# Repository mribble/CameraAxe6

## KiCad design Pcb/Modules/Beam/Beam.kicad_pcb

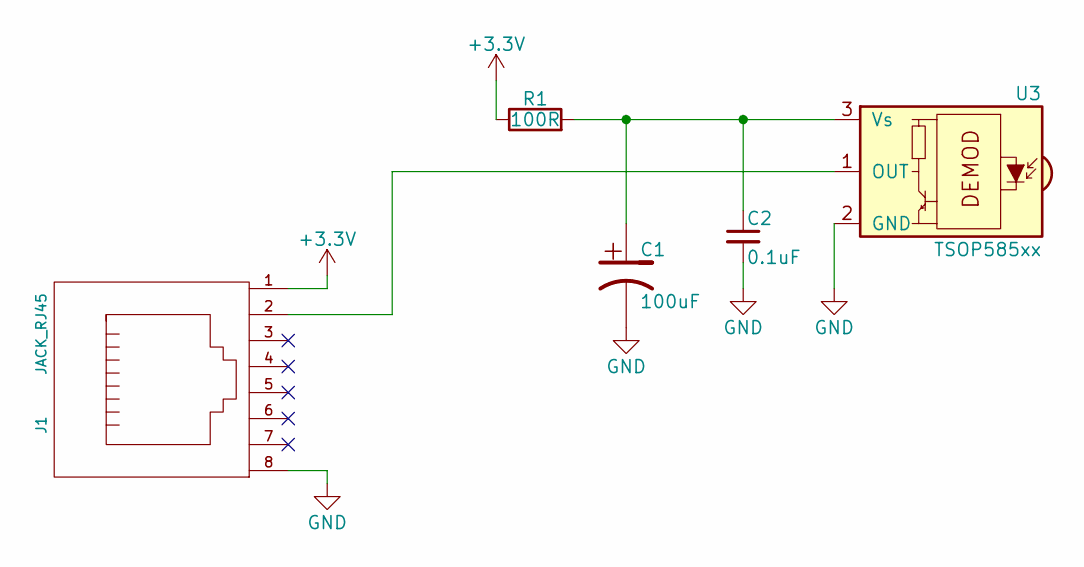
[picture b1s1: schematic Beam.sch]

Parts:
C1: 100uF; c_elec_6.3x5.7
C2: 0.1uF; R_0603
J1: JACK_RJ45; RJ45_pcbwing
R1: 100R; R_0603
U3: TSOP585xx; IRReceiver_Vishay_MINICAST-3pin

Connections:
+3V3: J1.1, R1.1
GND: C1.2, C2.2, J1.8, U3.2 (GND)
unnamed: C1.1, C2.1, R1.2, U3.3 (Vs)
unnamed: J1.2, U3.1 (OUT)

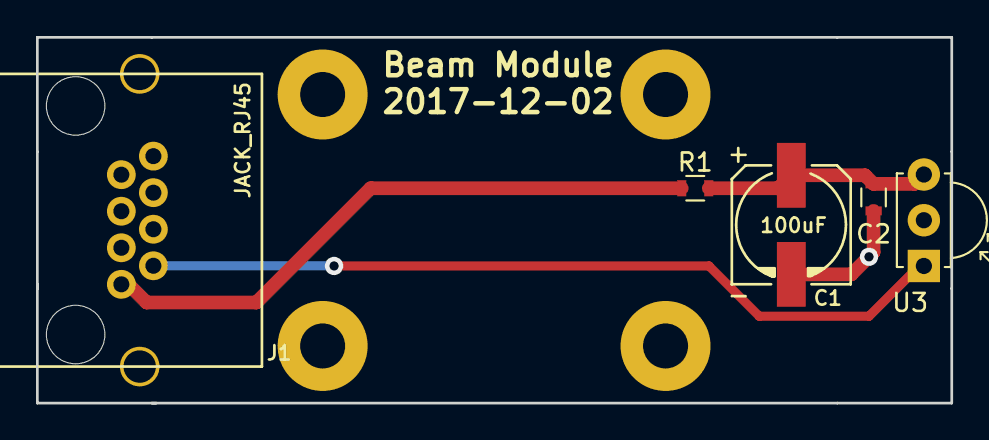
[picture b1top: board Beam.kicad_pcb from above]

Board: 2 copper layers, 50.8 x 20.3 mm, 9 parts (0 on the bottom side), 4 nets.

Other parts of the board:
X1, X2, X3, X4: HOLE; MountingHole_2.5mm_Pad

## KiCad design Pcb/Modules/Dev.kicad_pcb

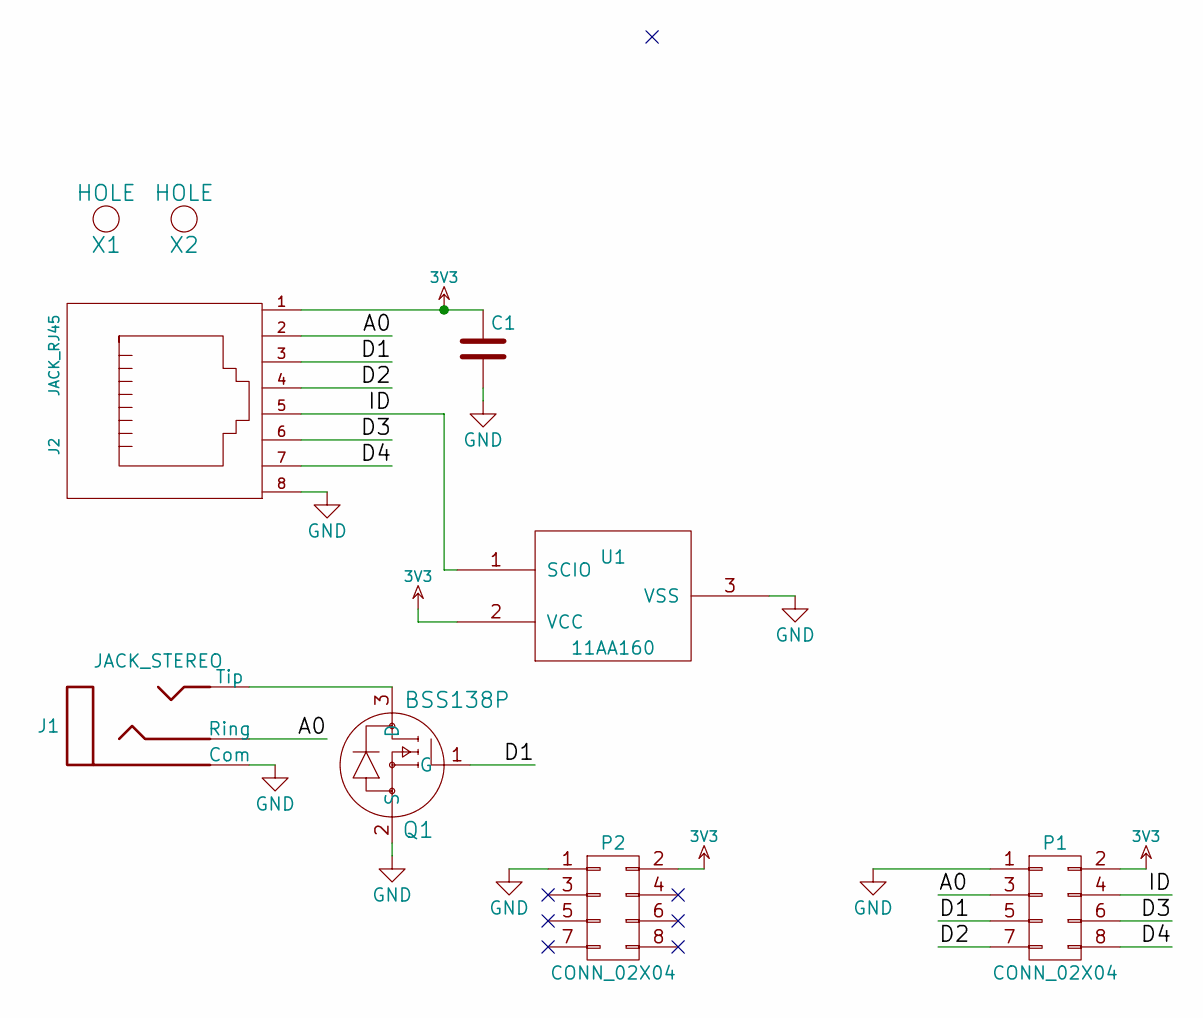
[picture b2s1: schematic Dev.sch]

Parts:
C1: C; c_1206
J1: JACK_STEREO; 161-3334-E_Big_Pad
J2: JACK_RJ45; RJ45_RJHSE-5080
P1, P2: CONN_02X04; Socket_Strip_Straight_2x04_Pitch2.54mm
Q1: BSS138P; SOT23
U1: 11AA160; SOT-23_11AA160
X1, X2: HOLE; HOLE_3.0mm

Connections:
3V3: C1.1, J2.1, P1.2, P2.2, U1.2 (VCC)
/A0: J1.1 (Ring), J2.2, P1.3
/D1: J2.3, P1.5, Q1.1 (G)
/D2: J2.4, P1.7
/D3: J2.6, P1.6
/D4: J2.7, P1.8
/ID: J2.5, P1.4, U1.1 (SCIO)
GND: C1.2, J1.3 (Com), J2.8, P1.1, P2.1, Q1.2 (S), U1.3 (VSS)
unnamed: J1.2 (Tip), Q1.3 (D)

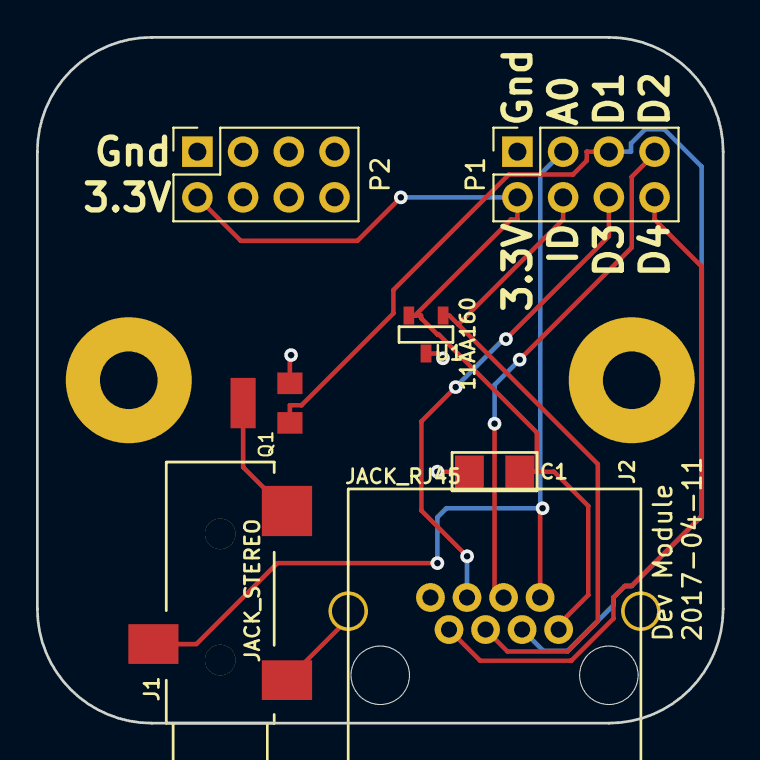
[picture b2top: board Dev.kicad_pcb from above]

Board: 2 copper layers, 38.1 x 38.1 mm, 9 parts (0 on the bottom side), 9 nets.

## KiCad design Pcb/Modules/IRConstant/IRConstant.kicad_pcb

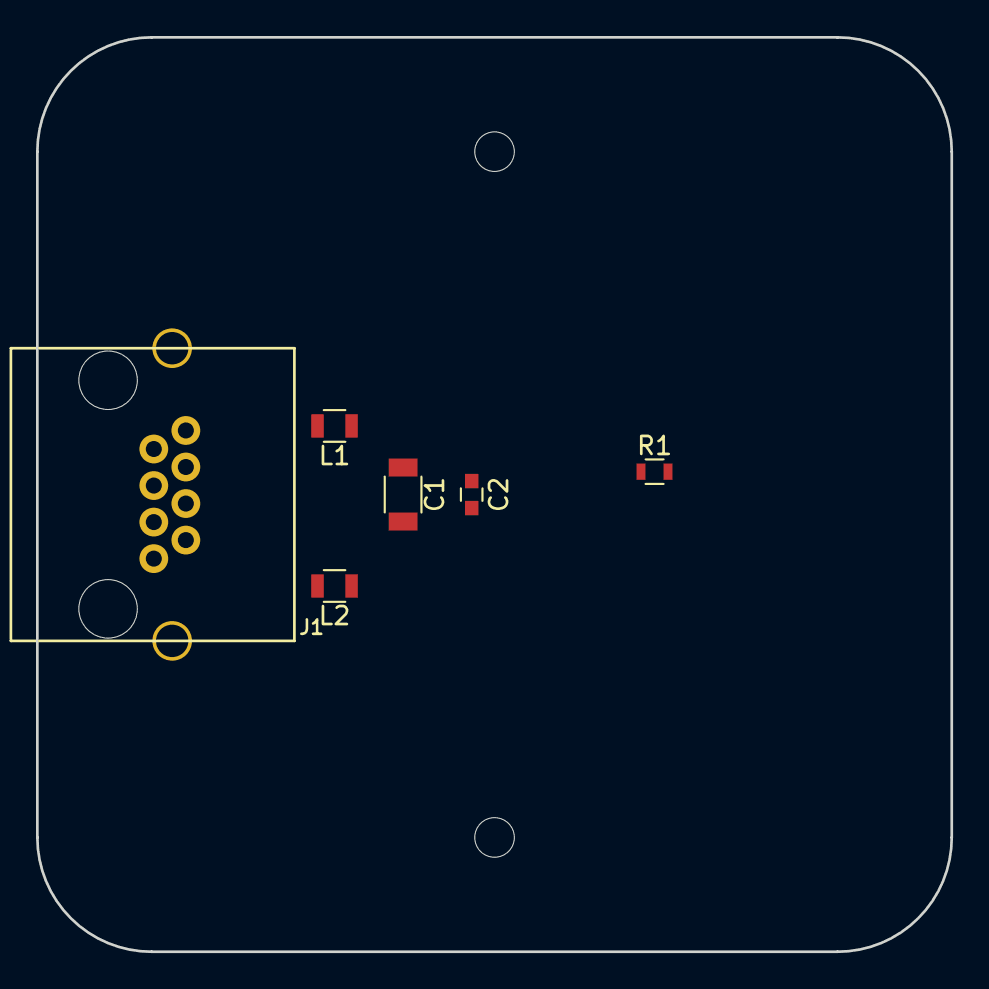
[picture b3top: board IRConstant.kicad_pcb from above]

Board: 2 copper layers, 50.8 x 50.8 mm, 6 parts (0 on the bottom side), 4 nets, no tracks yet.

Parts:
C1: 10uF; C_1206
C2: 0.1uF; C_0603
J1: JACK_RJ45; RJ45_pcbwing
L1, L2: Ferrite_Bead; R_0805
R1: R; R_0603

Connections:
+3V3: C1.1, C2.1, L1.1
GND: C1.2, C2.2, L2.1
unnamed: J1.1, L2.2
unnamed: J1.8, L1.2

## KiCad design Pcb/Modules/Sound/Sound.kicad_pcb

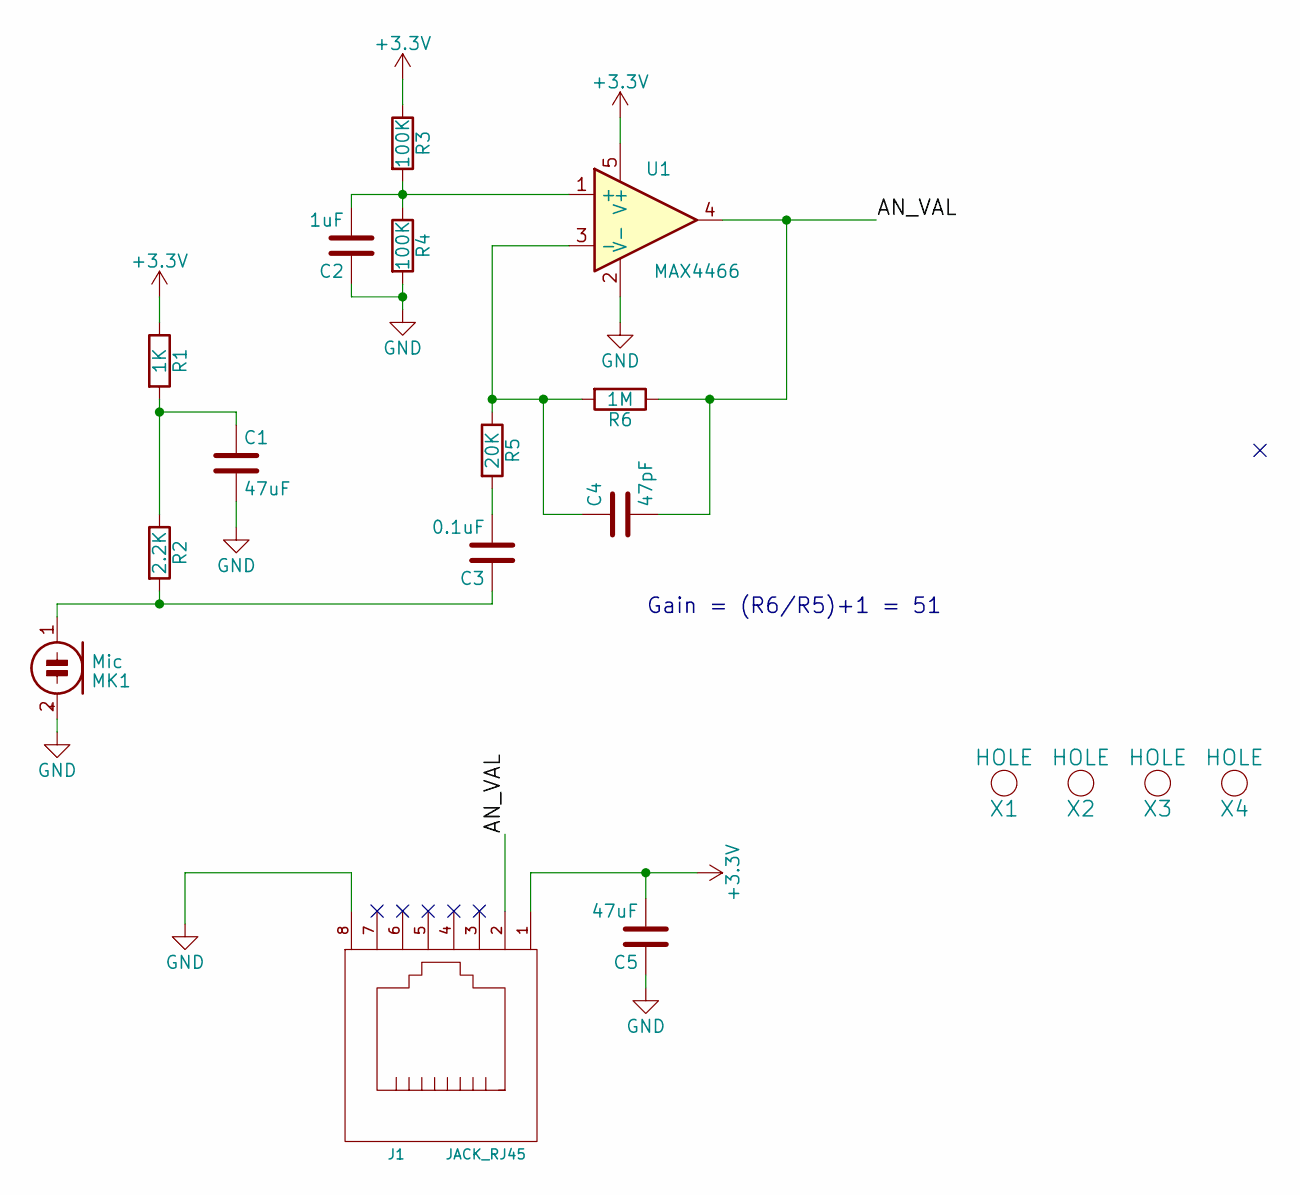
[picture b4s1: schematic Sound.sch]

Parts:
C1, C5: 47uF; C_1206
C2: 1uF; C_0603
C3: 0.1uF; C_0603
C4: 47pF; C_0603
J1: JACK_RJ45; RJ45_pcbwing
MK1: Mic; MIC_CMA-4544PF
R1: 1K; R_0603
R2: 2.2K; R_0603
R3, R4: 100K; R_0603
R5: 20K; R_0603
R6: 1M; R_0603
U1: MAX4466; SOT-353_SC-70-5
X1, X2, X3, X4: HOLE; MountingHole_2.5mm_Pad

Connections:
+3V3: C5.2, J1.1, R1.1, R3.1, U1.5 (V+)
/AN_VAL: C4.2, J1.2, R6.1, U1.4
GND: C1.2, C2.1, C5.1, J1.8, MK1.2 (+), R4.2, U1.2 (V-)
unnamed: C1.1, R1.2, R2.1
unnamed: C2.2, R3.2, R4.1, U1.1 (+)
unnamed: C3.1, MK1.1 (-), R2.2
unnamed: C3.2, R5.2
unnamed: C4.1, R5.1, R6.2, U1.3 (-)

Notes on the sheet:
Gain = (R6/R5)+1 = 51

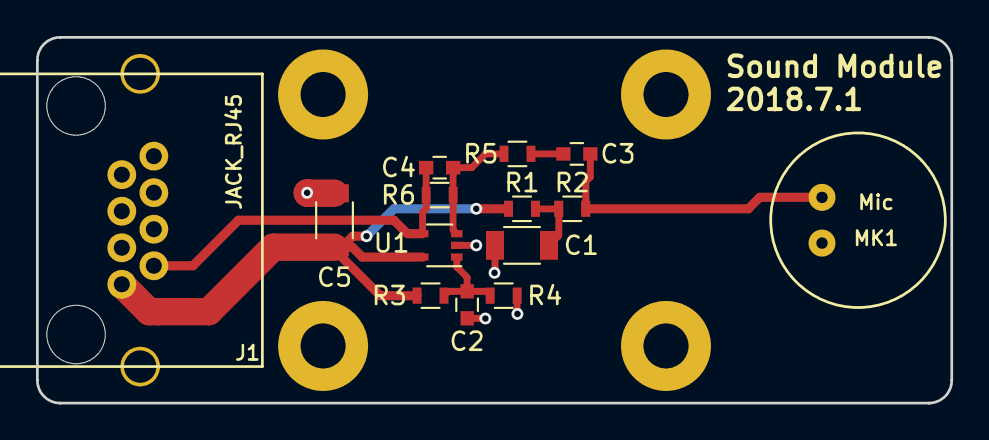
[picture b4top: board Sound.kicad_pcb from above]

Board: 2 copper layers, 50.8 x 20.3 mm, 18 parts (0 on the bottom side), 8 nets.

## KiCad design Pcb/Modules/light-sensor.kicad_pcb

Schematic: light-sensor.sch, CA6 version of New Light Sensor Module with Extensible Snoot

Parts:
C1: 10uF; c_1206
J1: JACK_RJ45; RJ45_pcbwing
J2: JACK_STEREO; 161-3334-E_Big_Pad
Q1: TEPT4400; PhotoTrans_Conn_Pads_1x02_Pitch2.54mm
Q2: MMBT2907ALT1G; SOT-23
R1, R3: 1K; SM0603_Resistor
R2: 174 1%; SM0805_Resistor
RV1: 20K; Potentiometer_Alps_RK09L_Single_Vertical
X1, X2, X3, X4: HOLE; MountingHole_2.2mm_M2

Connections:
3V3: C1.1, J1.1, Q1.3, Q2.2
/AN1: J1.2, R1.1
/D1: J1.3, R3.1
/D2: J1.4
/D3: J1.6
/D4: J1.7
/ID: J1.5
GND: C1.2, J1.8, J2.3 (Com), R2.2
unnamed: J2.2 (Tip), Q2.3
unnamed: Q1.1, R1.2, RV1.1
unnamed: Q2.1, R3.2
unnamed: R2.1, RV1.2, RV1.3

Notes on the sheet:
3.5mm Jack for Laser Power
Sensitivity Adj.
CA6 version of New Light Sensor Module with Extensible Snoot
just wire pads on board photo trans. connected via wires
Choose R2 for MAX current of 20mA 180 = 18.3 mA 174 = 18.9 mA 169 = 19.5 mA

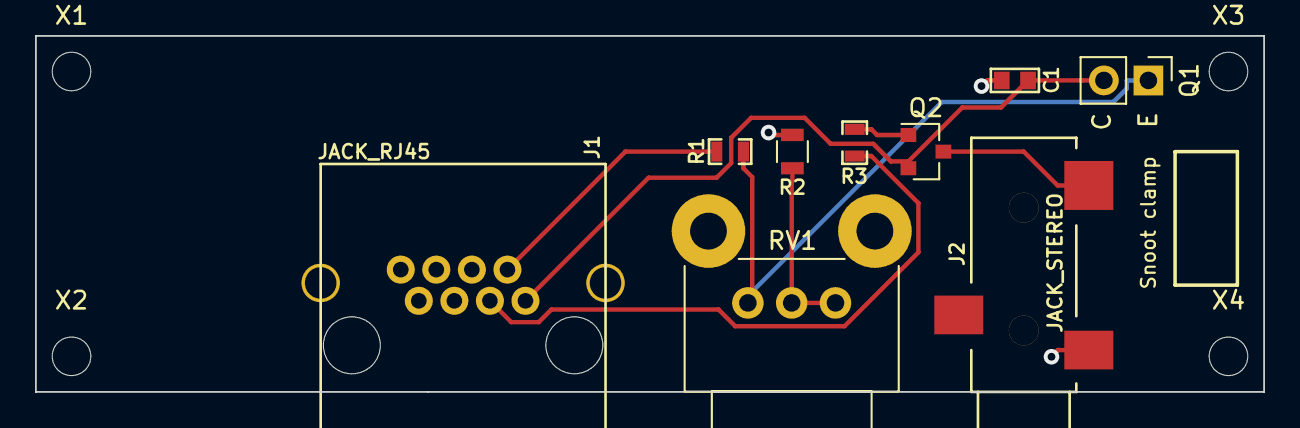
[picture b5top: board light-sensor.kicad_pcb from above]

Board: 2 copper layers, 70.1 x 20.3 mm, 13 parts (0 on the bottom side), 8 nets.

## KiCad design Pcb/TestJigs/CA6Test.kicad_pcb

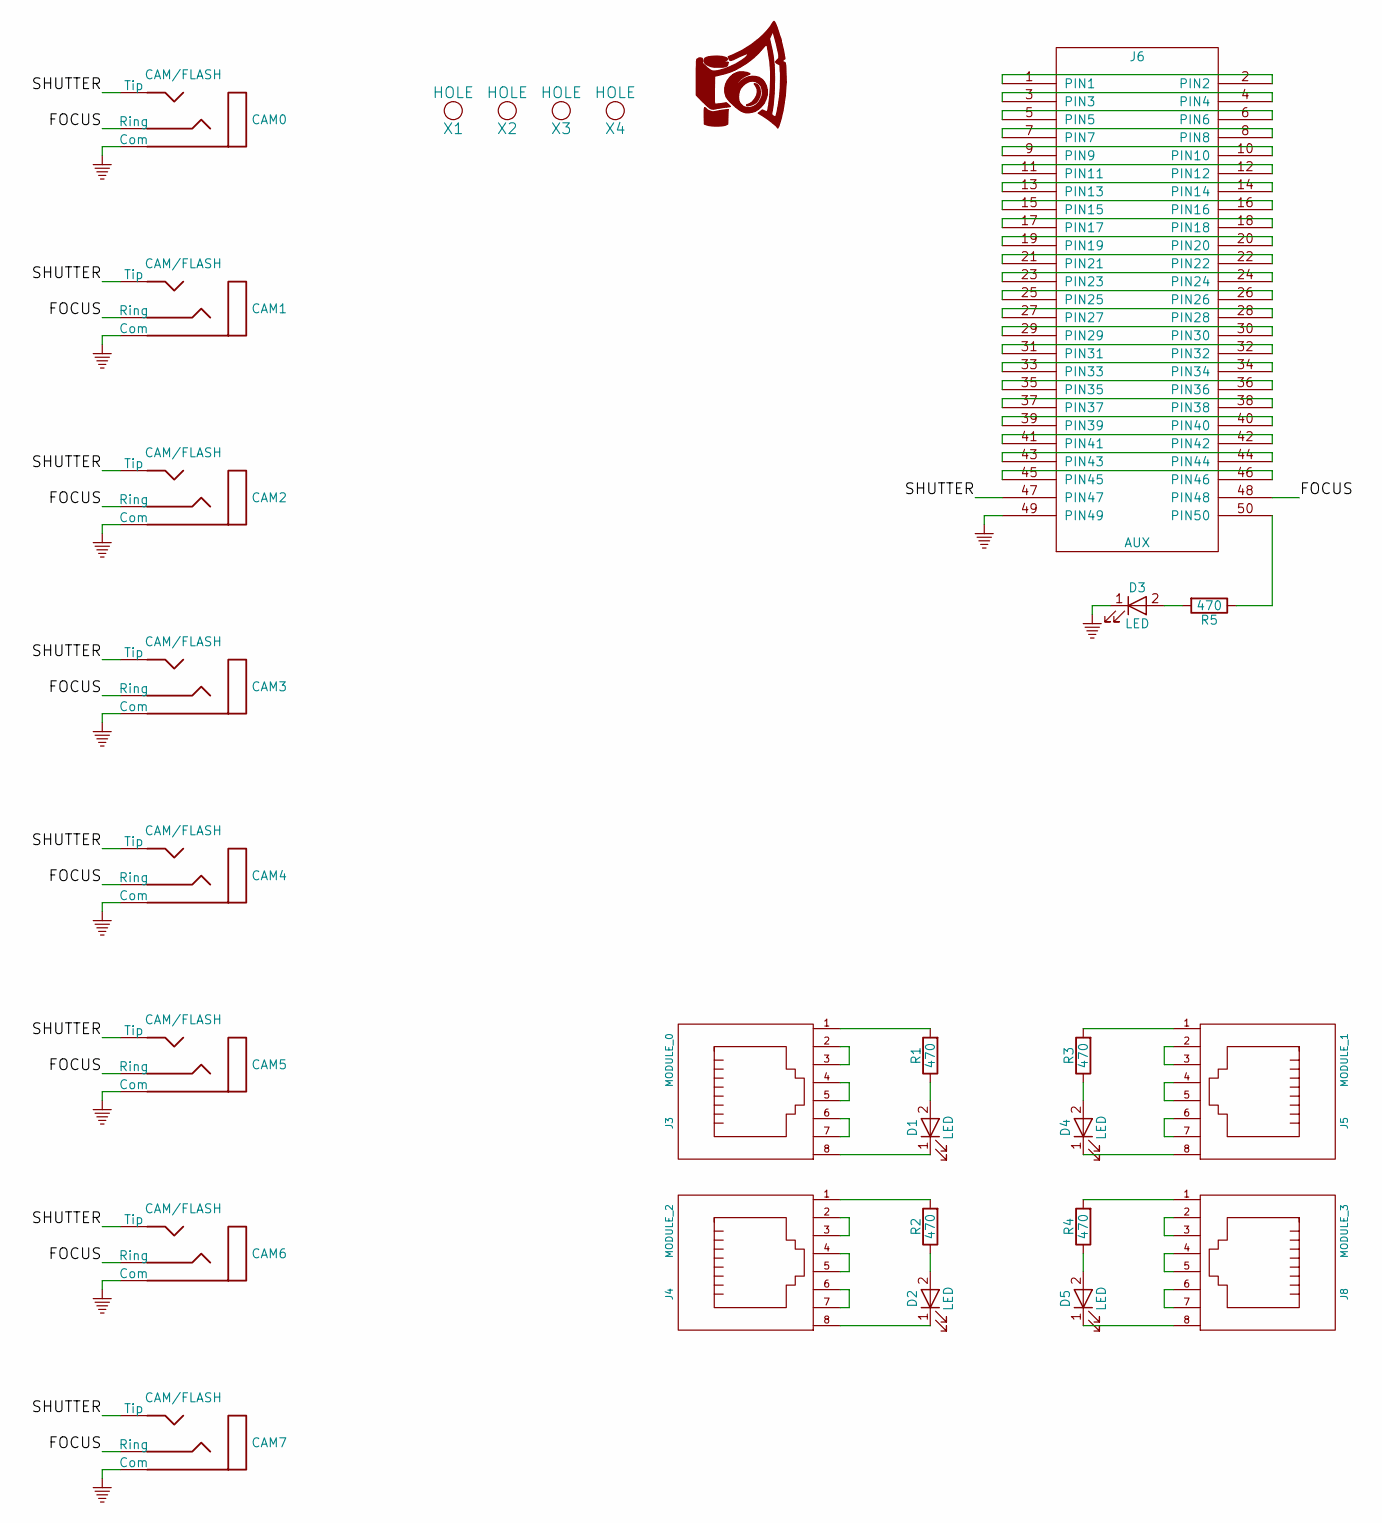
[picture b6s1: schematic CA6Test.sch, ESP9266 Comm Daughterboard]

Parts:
CAM0, CAM1, CAM2, CAM3, CAM4, CAM5, CAM6, CAM7: CAM/FLASH; 161-3334-E_Big_Pad
D1, D2, D3, D4, D5: LED; LED_D5.0mm
J3: MODULE_0; RJ45_pcbwing
J4: MODULE_2; RJ45_pcbwing
J5: MODULE_1; RJ45_pcbwing
J6: AUX; IDC_50PIN(2X25)-90
J8: MODULE_3; RJ45_pcbwing
LOGO1: CA_LOGO_150; CA_Logo_15mm
R1, R2, R3, R4, R5: 470; R_Axial_DIN0309_L9.0mm_D3.2mm_P12.70mm_Horizontal
X1, X2, X3, X4: HOLE; HOLE_3.0mm

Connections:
/FOCUS: CAM0.1 (Ring), CAM1.1 (Ring), CAM2.1 (Ring), CAM3.1 (Ring), CAM4.1 (Ring), CAM5.1 (Ring), CAM6.1 (Ring), CAM7.1 (Ring), J6.48 (PIN48)
/SHUTTER: CAM0.2 (Tip), CAM1.2 (Tip), CAM2.2 (Tip), CAM3.2 (Tip), CAM4.2 (Tip), CAM5.2 (Tip), CAM6.2 (Tip), CAM7.2 (Tip), J6.47 (PIN47)
GND: CAM0.3 (Com), CAM1.3 (Com), CAM2.3 (Com), CAM3.3 (Com), CAM4.3 (Com), CAM5.3 (Com), CAM6.3 (Com), CAM7.3 (Com), D3.1 (K), J6.49 (PIN49)
unnamed: D1.1 (K), J3.8
unnamed: D1.2 (A), R1.1
unnamed: D2.1 (K), J4.8
unnamed: D2.2 (A), R2.1
unnamed: D3.2 (A), R5.2
unnamed: D4.1 (K), J5.8
unnamed: D4.2 (A), R3.1
unnamed: D5.1 (K), J8.8
unnamed: D5.2 (A), R4.1
unnamed: J3.1, R1.2
unnamed: J3.2, J3.3
unnamed: J3.4, J3.5
unnamed: J3.6, J3.7
unnamed: J4.1, R2.2
unnamed: J4.2, J4.3
unnamed: J4.4, J4.5
unnamed: J4.6, J4.7
unnamed: J5.1, R3.2
unnamed: J5.2, J5.3
unnamed: J5.4, J5.5
unnamed: J5.6, J5.7
unnamed: J6.1 (PIN1), J6.2 (PIN2)
unnamed: J6.3 (PIN3), J6.4 (PIN4)
unnamed: J6.5 (PIN5), J6.6 (PIN6)
unnamed: J6.7 (PIN7), J6.8 (PIN8)
unnamed: J6.9 (PIN9), J6.10 (PIN10)
unnamed: J6.11 (PIN11), J6.12 (PIN12)
unnamed: J6.13 (PIN13), J6.14 (PIN14)
unnamed: J6.15 (PIN15), J6.16 (PIN16)
unnamed: J6.17 (PIN17), J6.18 (PIN18)
unnamed: J6.19 (PIN19), J6.20 (PIN20)
unnamed: J6.21 (PIN21), J6.22 (PIN22)
unnamed: J6.23 (PIN23), J6.24 (PIN24)
unnamed: J6.25 (PIN25), J6.26 (PIN26)
unnamed: J6.27 (PIN27), J6.28 (PIN28)
unnamed: J6.29 (PIN29), J6.30 (PIN30)
unnamed: J6.31 (PIN31), J6.32 (PIN32)
unnamed: J6.33 (PIN33), J6.34 (PIN34)
unnamed: J6.35 (PIN35), J6.36 (PIN36)
unnamed: J6.37 (PIN37), J6.38 (PIN38)
unnamed: J6.39 (PIN39), J6.40 (PIN40)
unnamed: J6.41 (PIN41), J6.42 (PIN42)
unnamed: J6.43 (PIN43), J6.44 (PIN44)
unnamed: J6.45 (PIN45), J6.46 (PIN46)
unnamed: J6.50 (PIN50), R5.1
unnamed: J8.1, R4.2
unnamed: J8.2, J8.3
unnamed: J8.4, J8.5
unnamed: J8.6, J8.7

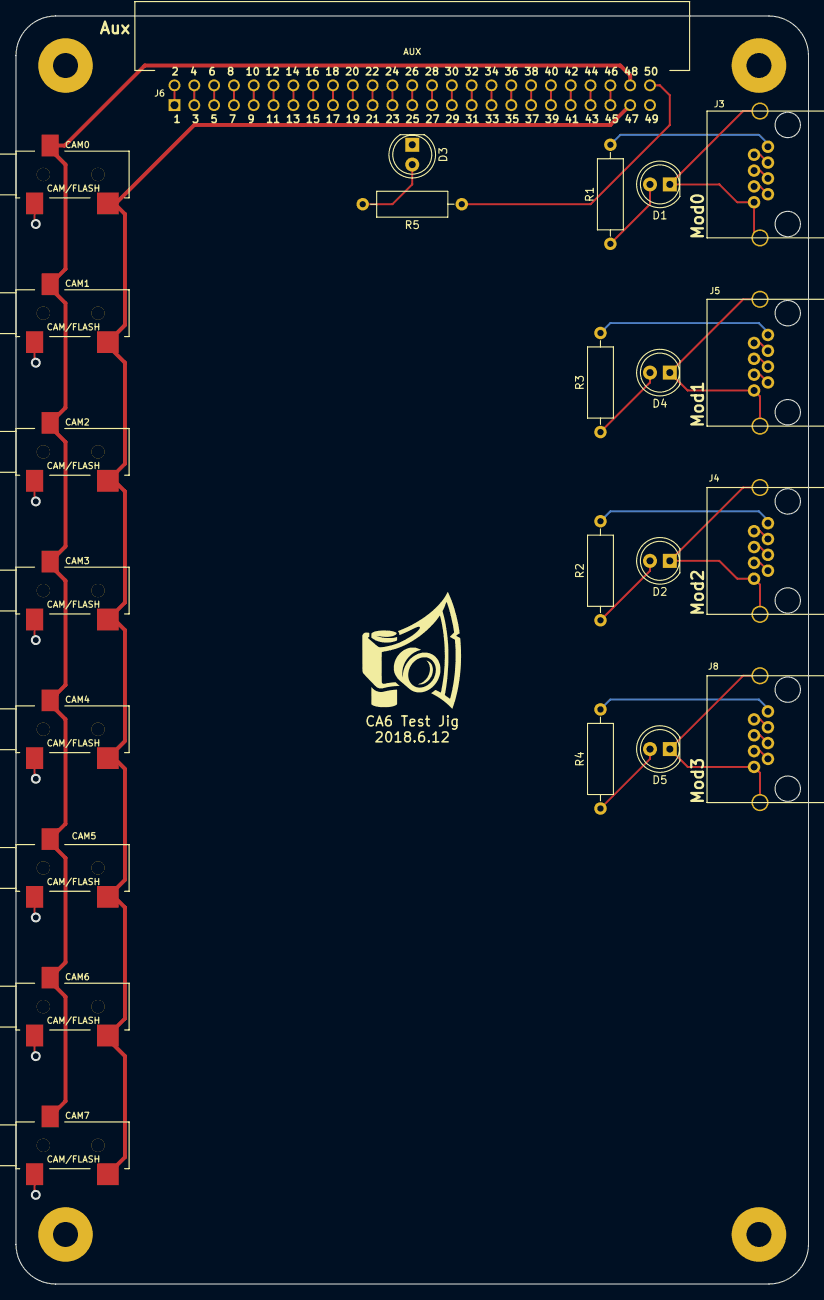
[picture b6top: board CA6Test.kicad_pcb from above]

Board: 2 copper layers, 101.6 x 162.6 mm, 28 parts (0 on the bottom side), 52 nets.
